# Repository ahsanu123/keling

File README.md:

<p>

</p>

<p align="center">
   <b> Keling - DAP Link Collection </b>
</p> 

- pikolink CMSIS DAP with RP2040 and yapicoprobe
- weling CMSIS DAP With CH55x and sdcc

## 🐑 References

- make new project Piko, picoprobe based on https://github.com/ErichStyger/mcuoneclipse/tree/master/KiCAD/Projects/PicoLink
- wagiminator ch552 daplink https://github.com/wagiminator/CH552-DAPLink
- yapicoprobe https://github.com/rgrr/yapicoprobe/blob/master/doc/hardware.adoc
- mcu on eclipse picolink https://mcuoneclipse.com/2023/04/08/open-source-picolink-raspberry-pi-rp2040-cmsis-dap-debug-probe/

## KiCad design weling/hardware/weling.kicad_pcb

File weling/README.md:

<h1> 🐍 Weling </h1>
<p>

</p>

<p align="center">CMSIS DAP Probe With CH552G</p>

### 🧺 Schematic

## 🌳 Log

- 1 Oktober 2025, ⏰ 19:37. Finish Make Schematic and Routing.

## 🩹 Rerence

- CH55x Library ->  https://github.com/devbisme/KiCad-Schematic-Symbol-Libraries/blob/master/wch.lib

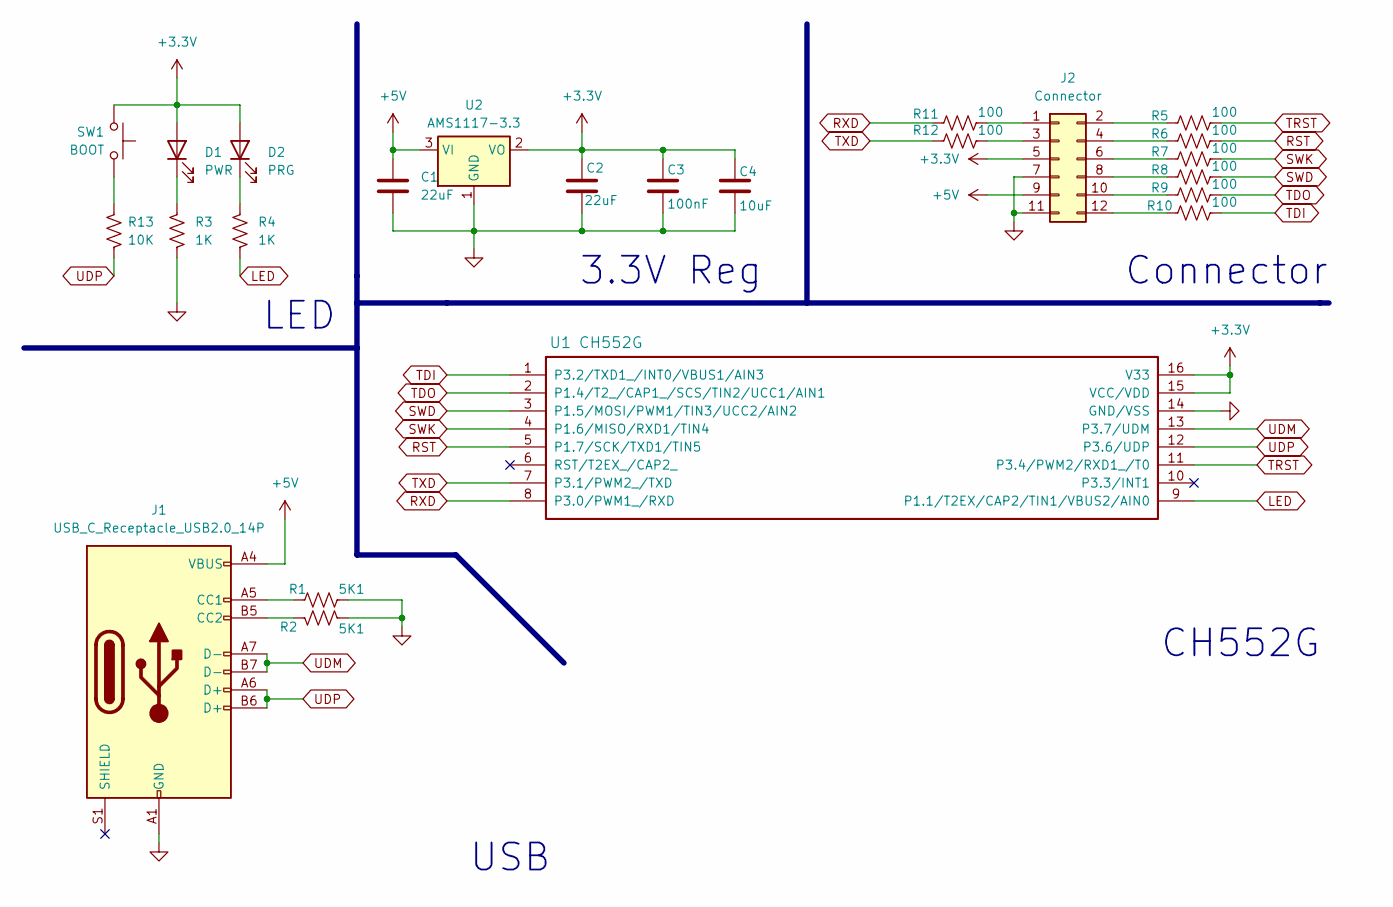
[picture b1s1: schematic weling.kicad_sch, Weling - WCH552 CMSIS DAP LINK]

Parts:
C1, C2: 22uF; C_0805_2012Metric_Pad1.18x1.45mm_HandSolder
C3: 100nF; C_0805_2012Metric_Pad1.18x1.45mm_HandSolder
C4: 10uF; C_0805_2012Metric_Pad1.18x1.45mm_HandSolder
D1: PWR; LED_1206_3216Metric_Pad1.42x1.75mm_HandSolder
D2: PRG; LED_1206_3216Metric_Pad1.42x1.75mm_HandSolder
J1: USB_C_Receptacle_USB2.0_14P; USB_C_Receptacle_GCT_USB4110
J2: Connector; IDC-Header_2x06_P2.54mm_Vertical
R1, R2: 5K1; R_0805_2012Metric_Pad1.20x1.40mm_HandSolder
R3, R4: 1K; R_0805_2012Metric_Pad1.20x1.40mm_HandSolder
R5, R6, R7, R8, R9, R10, R11, R12: 100; R_0805_2012Metric_Pad1.20x1.40mm_HandSolder
R13: 10K; R_0805_2012Metric_Pad1.20x1.40mm_HandSolder
SW1: BOOT; SW_Push_1P1T_NO_6x6mm_H9.5mm
U1: CH552G; STC_SOP-16_3.9x9.9mm_P1.27mm
U2: AMS1117-3.3; SOT-223-3_TabPin2

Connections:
+3.3V: C2.1, C3.1, C4.1, D1.2 (A), D2.2 (A), J2.5, SW1.2, U1.15 (VCC/VDD), U1.16 (V33), U2.2 (VO)
+5V: C1.1, J1.A4 (VBUS), J1.A9 (VBUS), J1.B4 (VBUS), J1.B9 (VBUS), J2.9, U2.3 (VI)
GND: C1.2, C2.2, C3.2, C4.2, J1.A1 (GND), J1.A12 (GND), J1.B1 (GND), J1.B12 (GND), J2.7, J2.11, R1.2, R2.2, R3.1, U1.14 (GND/VSS), U2.1 (GND)
LED: R4.1, U1.9 (P1.1/T2EX/CAP2/TIN1/VBUS2/AIN0)
unnamed: D1.1 (K), R3.2
unnamed: D2.1 (K), R4.2
unnamed: J1.A5 (CC1), R1.1
unnamed: J1.B5 (CC2), R2.1
unnamed: J2.1, R11.2
unnamed: J2.2, R5.1
unnamed: J2.3, R12.2
unnamed: J2.4, R6.1
unnamed: J2.6, R7.1
unnamed: J2.8, R8.1
unnamed: J2.10, R9.1
unnamed: J2.12, R10.1
unnamed: R13.2, SW1.1
RST: R6.2, U1.5 (P1.7/SCK/TXD1/TIN5)
RXD: R11.1, U1.8 (P3.0/PWM1_/RXD)
SWD: R8.2, U1.3 (P1.5/MOSI/PWM1/TIN3/UCC2/AIN2)
SWK: R7.2, U1.4 (P1.6/MISO/RXD1/TIN4)
TDI: R10.2, U1.1 (P3.2/TXD1_/INT0/VBUS1/AIN3)
TDO: R9.2, U1.2 (P1.4/T2_/CAP1_/SCS/TIN2/UCC1/AIN1)
TRST: R5.2, U1.11 (P3.4/PWM2/RXD1_/T0)
TXD: R12.1, U1.7 (P3.1/PWM2_/TXD)
UDM: J1.A7 (D-), J1.B7 (D-), U1.13 (P3.7/UDM)
UDP: J1.A6 (D+), J1.B6 (D+), R13.1, U1.12 (P3.6/UDP)

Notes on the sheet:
3.3V Reg
LED
USB
Connector
CH552G

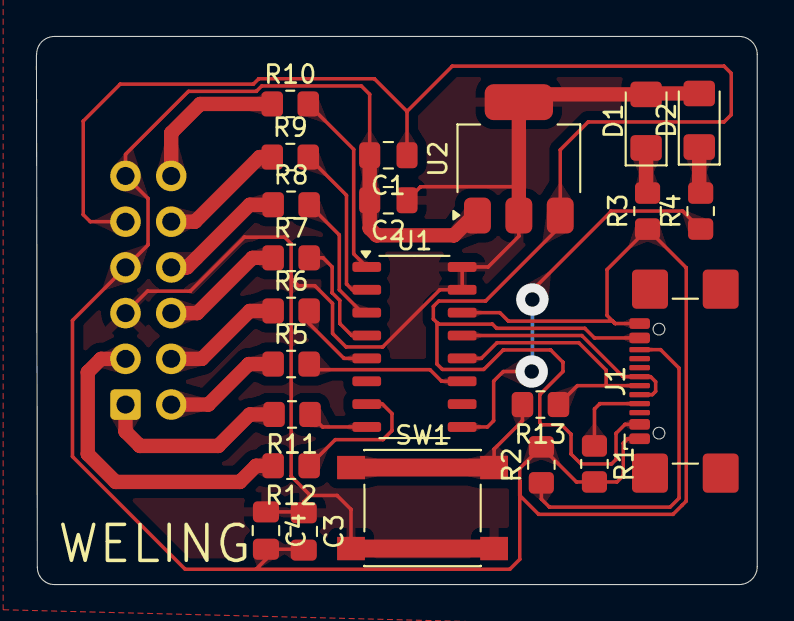
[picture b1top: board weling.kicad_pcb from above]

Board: 2 copper layers, 40.0 x 30.5 mm, 24 parts (1 on the bottom side), 27 nets.

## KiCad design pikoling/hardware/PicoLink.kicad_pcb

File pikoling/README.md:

<h1>🐤 piko </h1>
<p>

</p>

<p align="center">CMSIS DAP Probe</p>

### 🧺 Schematic

## 🌳 Log

- 12 September 2025, ⏰ 19:17. success to flash [yapicoprobe-0124-pico-9aff542.uf2](https://github.com/rgrr/yapicoprobe/releases/tag/v1.24) firmware
  - to upload firmware connect usb c to pc while press reset button, there will new usb mass device detected, copy `uf2` file into that rp2040 usb mass device, and chip will be flashed.
- 12 September 2025, ⏰ 19:49, 🐛 BUG 1, remove 100 ohm resistor between SWDIO, SWCLK and pinhead connector, adding 100 ohm resistor make probing not work.

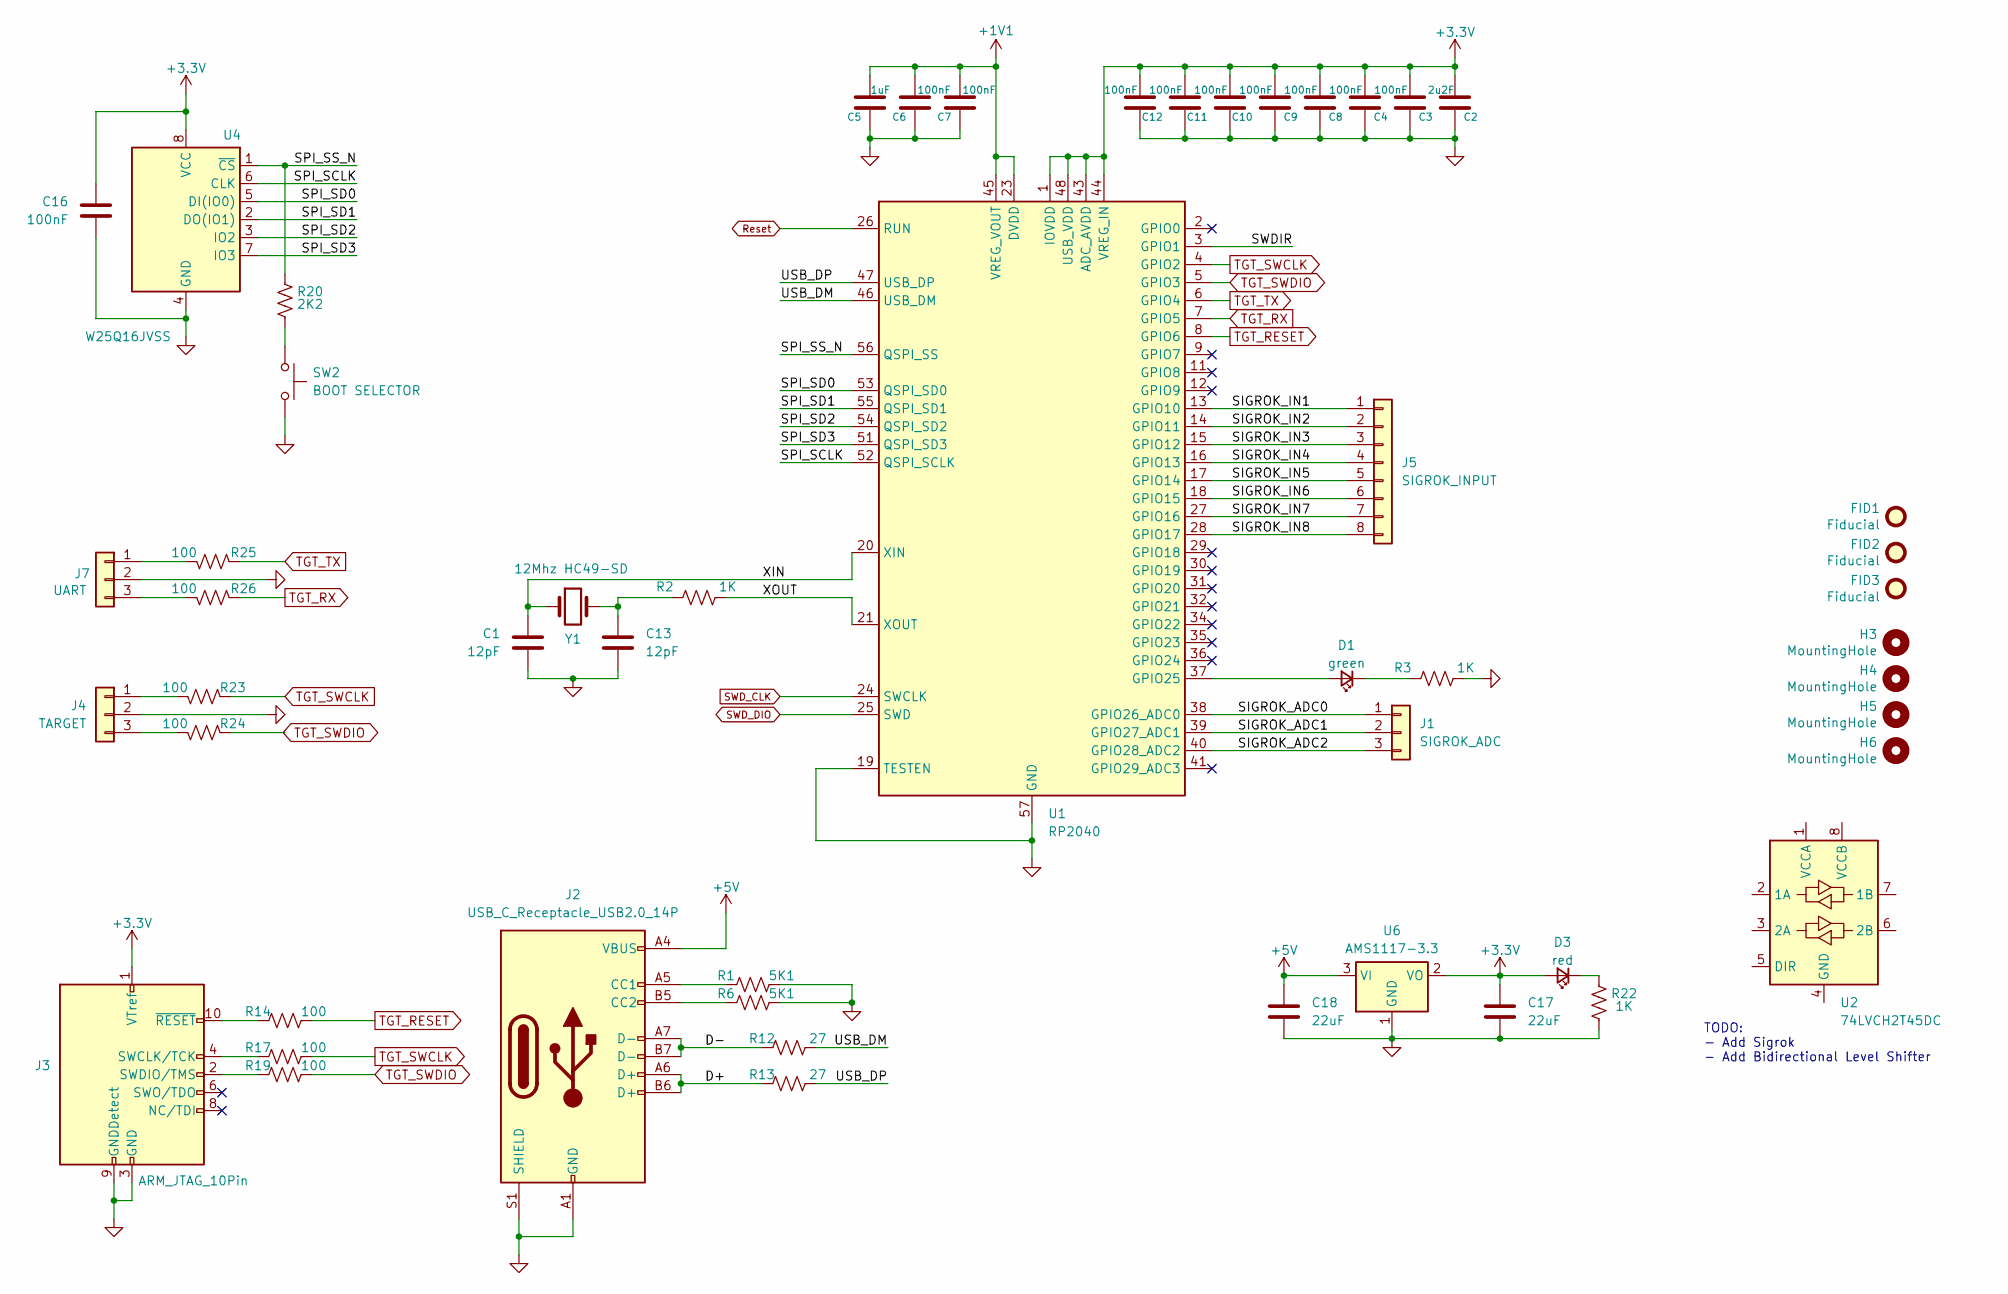
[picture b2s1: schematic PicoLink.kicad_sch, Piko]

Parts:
C1, C13: 12pF; C_0603_1608Metric_Pad1.08x0.95mm_HandSolder
C2: 2u2F; C_0603_1608Metric_Pad1.08x0.95mm_HandSolder
C3, C4, C6, C7, C8, C9, C10, C11, C12, C16: 100nF; C_0603_1608Metric_Pad1.08x0.95mm_HandSolder
C5: 1uF; C_0603_1608Metric_Pad1.08x0.95mm_HandSolder
C17, C18: 22uF; C_0603_1608Metric_Pad1.08x0.95mm_HandSolder
D1: green; LED_0805_2012Metric_Pad1.15x1.40mm_HandSolder; mouser# 78-VLMTG1300-GS08
D3: red; LED_0805_2012Metric_Pad1.15x1.40mm_HandSolder; mouser# 78-VLMS1300-GS08
FID1, FID2, FID3: Fiducial; Fiducial_1mm_Mask2mm
H3, H4, H5, H6: MountingHole; MountingHole_2.7mm_M2.5
J1: SIGROK_ADC; PinHeader_1x03_P2.54mm_Vertical
J2: USB_C_Receptacle_USB2.0_14P; USB_C_Receptacle_GCT_USB4110
J3: ARM_JTAG_10Pin; IDC-Header_2x05_P2.54mm_Vertical
J4: TARGET; PinHeader_1x03_P2.54mm_Vertical
J5: SIGROK_INPUT; PinHeader_1x07_P2.54mm_Vertical
J7: UART; PinHeader_1x03_P2.54mm_Vertical
R1, R6: 5K1; R_0805_2012Metric_Pad1.20x1.40mm_HandSolder
R2, R3, R22: 1K; R_0805_2012Metric_Pad1.20x1.40mm_HandSolder
R12, R13: 27; R_0805_2012Metric_Pad1.20x1.40mm_HandSolder
R14, R17, R19, R23, R24, R25, R26: 100; R_0805_2012Metric_Pad1.20x1.40mm_HandSolder
R20: 2K2; R_0805_2012Metric_Pad1.20x1.40mm_HandSolder
SW2: BOOT SELECTOR; SW_Push_1P1T_NO_6x6mm_H9.5mm
U1: RP2040; QFN-56-1EP_7x7mm_P0.4mm_EP3.2x3.2mm
U2: 74LVCH2T45DC; VSSOP-8_2.3x2mm_P0.5mm
U4: W25Q16JVSS; SOIC-8_5.23x5.23mm_P1.27mm
U6: AMS1117-3.3; SOT-223-3_TabPin2
Y1: 12Mhz HC49-SD; Crystal_SMD_HC49-SD

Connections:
+1V1: C5.1, C6.1, C7.1, U1.23 (DVDD), U1.45 (VREG_VOUT), U1.50 (DVDD)
+3.3V: C2.1, C3.1, C4.1, C8.1, C9.1, C10.1, C11.1, C12.1, C16.1, C17.1, D3.2 (A), J3.1 (VTref), U1.1 (IOVDD), U1.10 (IOVDD), U1.22 (IOVDD), U1.33 (IOVDD), U1.42 (IOVDD), U1.43 (ADC_AVDD), U1.44 (VREG_IN), U1.48 (USB_VDD), U1.49 (IOVDD), U4.8 (VCC), U6.2 (VO)
+5V: C18.1, J2.A4 (VBUS), J2.A9 (VBUS), J2.B4 (VBUS), J2.B9 (VBUS), U6.3 (VI)
/D+: J2.A6 (D+), J2.B6 (D+), R13.1
/D-: J2.A7 (D-), J2.B7 (D-), R12.1
/SIGROK_ADC0: J1.1, U1.38 (GPIO26_ADC0)
/SIGROK_ADC1: J1.2, U1.39 (GPIO27_ADC1)
/SIGROK_ADC2: J1.3, U1.40 (GPIO28_ADC2)
/SIGROK_IN1: J5.1, U1.13 (GPIO10)
/SIGROK_IN2: J5.2, U1.14 (GPIO11)
/SIGROK_IN3: J5.3, U1.15 (GPIO12)
/SIGROK_IN4: J5.4, U1.16 (GPIO13)
/SIGROK_IN5: J5.5, U1.17 (GPIO14)
/SIGROK_IN6: J5.6, U1.18 (GPIO15)
/SIGROK_IN7: J5.7, U1.27 (GPIO16)
/SIGROK_IN8: J5.8, U1.28 (GPIO17)
/SPI_SCLK: U1.52 (QSPI_SCLK), U4.6 (CLK)
/SPI_SD0: U1.53 (QSPI_SD0), U4.5 (DI(IO0))
/SPI_SD1: U1.55 (QSPI_SD1), U4.2 (DO(IO1))
/SPI_SD2: U1.54 (QSPI_SD2), U4.3 (IO2)
/SPI_SD3: U1.51 (QSPI_SD3), U4.7 (IO3)
/SPI_SS_N: R20.1, U1.56 (QSPI_SS), U4.1 (~CS)
/SWDIR: U1.3 (GPIO1)
/USB_DM: R12.2, U1.46 (USB_DM)
/USB_DP: R13.2, U1.47 (USB_DP)
/XIN: C1.1, U1.20 (XIN), Y1.1
/XOUT: R2.2, U1.21 (XOUT)
GND: C1.2, C2.2, C3.2, C4.2, C5.2, C6.2, C7.2, C8.2, C9.2, C10.2, C11.2, C12.2, C13.2, C16.2, C17.2, C18.2, J2.A1 (GND), J2.A12 (GND), J2.B1 (GND), J2.B12 (GND), J2.S1 (SHIELD), J3.3 (GND), J3.5 (GND), J3.9 (GNDDetect), J4.2, J7.2, R1.2, R3.2, R6.2, R22.2, SW2.2, U1.19 (TESTEN), U1.57 (GND), U4.4 (GND), U6.1 (GND)
unnamed: C13.1, R2.1, Y1.2
unnamed: D1.2 (A), U1.37 (GPIO25)
unnamed: D1.1 (K), R3.1
unnamed: D3.1 (K), R22.1
unnamed: J2.A5 (CC1), R1.1
unnamed: J2.B5 (CC2), R6.1
unnamed: J3.4 (SWCLK/TCK), R17.1
unnamed: J3.2 (SWDIO/TMS), R19.1
unnamed: J3.10 (~RESET), R14.1
unnamed: J4.1, R23.2
unnamed: J4.3, R24.2
unnamed: J7.1, R25.2
unnamed: J7.3, R26.2
unnamed: R20.2, SW2.1
Reset: U1.26 (RUN)
SWD_CLK: U1.24 (SWCLK)
SWD_DIO: U1.25 (SWD)
TGT_RESET: R14.2, U1.8 (GPIO6)
TGT_RX: R26.1, U1.7 (GPIO5)
TGT_SWCLK: R17.2, R23.1, U1.4 (GPIO2)
TGT_SWDIO: R19.2, R24.1, U1.5 (GPIO3)
TGT_TX: R25.1, U1.6 (GPIO4)

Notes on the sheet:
TODO: - Add Sigrok - Add Bidirectional Level Shifter

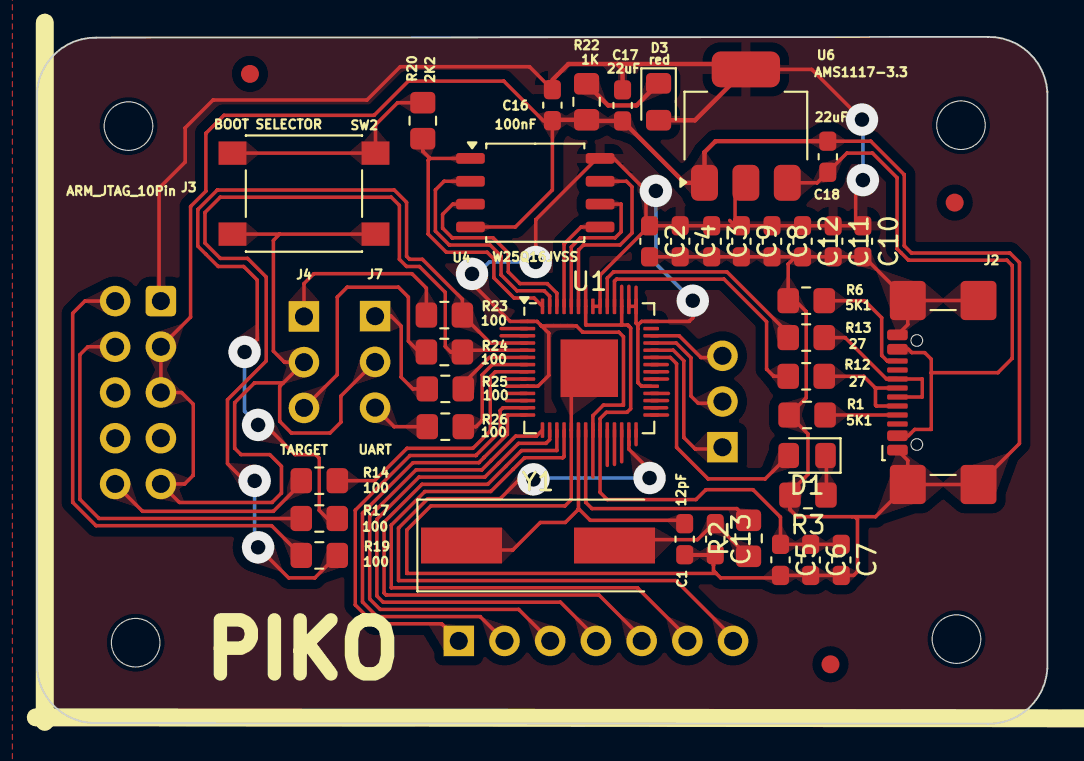
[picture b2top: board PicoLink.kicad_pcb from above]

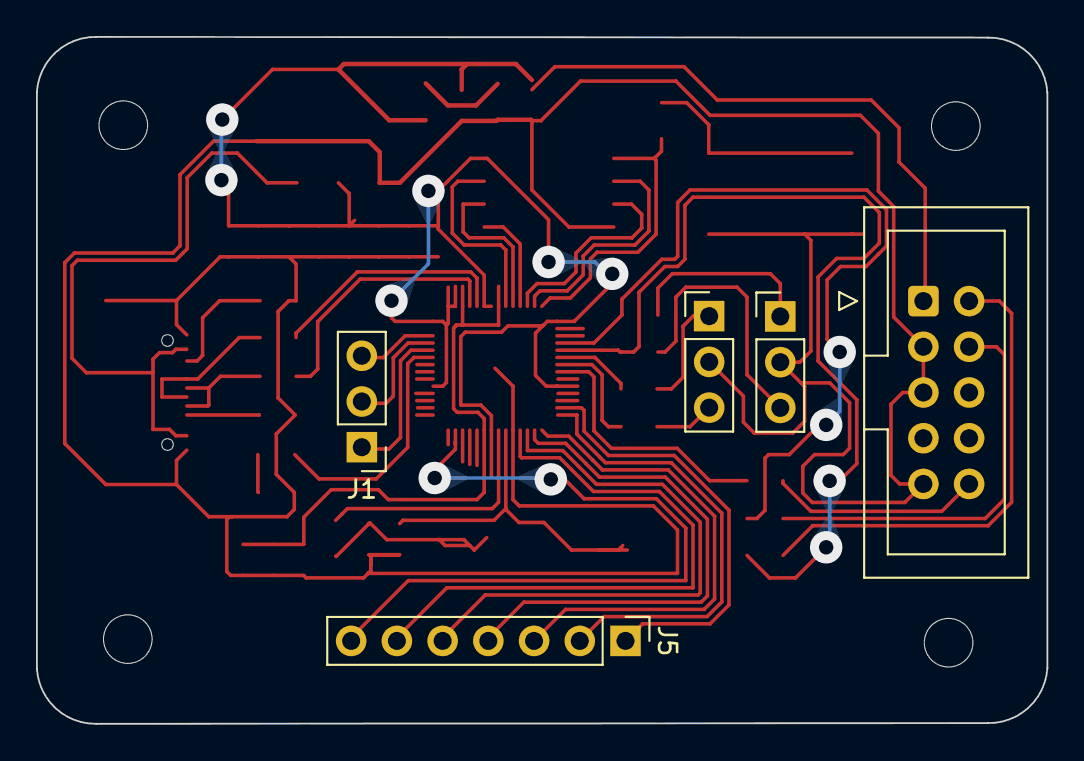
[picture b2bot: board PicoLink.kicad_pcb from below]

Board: 2 copper layers, 56.1 x 38.2 mm, 51 parts (5 on the bottom side), 45 nets.

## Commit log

2025-07-20 [07-20-0908] update gerber and schematic
2025-09-13 feat: add lightburn project
2025-09-30 fork: copying ch552 dap link from wagiminator to weling
2025-10-01 feat: complete schematic and basic routing, need to recheck
    n
    Rename README.md to README_Original.md
    p
    Update README.md
2025-10-02 feat: add decoupling capacitor
